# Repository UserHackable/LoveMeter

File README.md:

## LoveMeter 

### Board dimensions

* (390000, 110000) original units
* (3.9000, 1.1000) inches
* (99.0600, 27.9400) mm

[gerbers](%*_gerber.zip)

| Front | Back |
| --- | --- |
|  |  |

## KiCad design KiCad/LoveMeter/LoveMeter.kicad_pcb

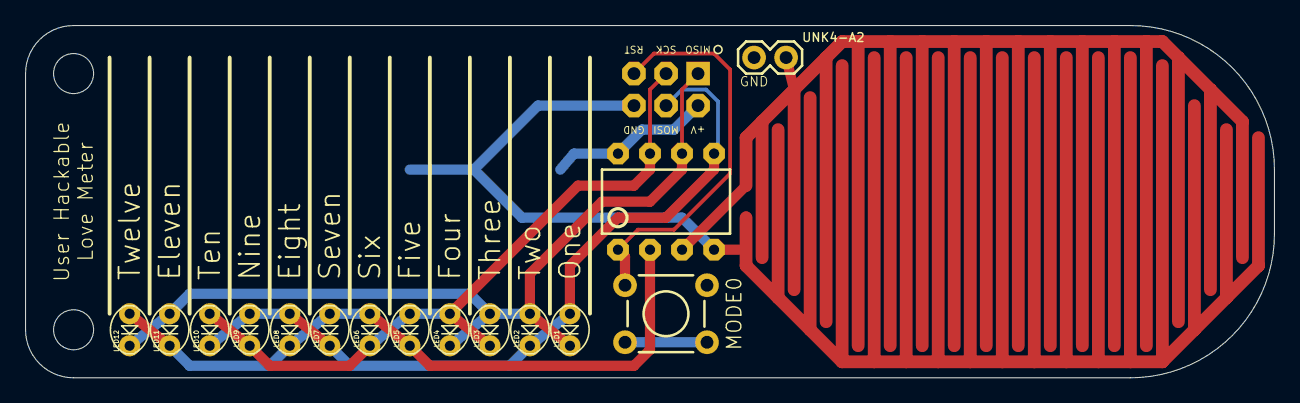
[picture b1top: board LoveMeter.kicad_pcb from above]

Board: 2 copper layers, 99.1 x 27.9 mm, 20 parts (1 on the bottom side), 8 nets.

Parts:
J1: AVR_SPI; 2X3-NS
LED1, LED2, LED3, LED4, LED5, LED6, LED7, LED8, LED9, LED10, LED11, LED12: LED-OVAL
MODE0: TACTILE-PTH
U1: TINY85; DIP08
U$3: THUMB_PAD
U$4: CR2032_STRAP
UNK4-A2: 1X02
UNK_HOLE_0: dummyfp0
UNK_HOLE_1: dummyfp1

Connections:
B0: J1.4, LED1.ANODE, LED2.CATHODE, LED7.CATHODE, LED8.ANODE, LED9.ANODE, LED10.CATHODE, U1.5
B1: J1.1, LED1.CATHODE, LED2.ANODE, LED3.ANODE, LED4.CATHODE, LED11.ANODE, LED12.CATHODE, U1.6
B2: J1.3, LED3.CATHODE, LED4.ANODE, LED5.ANODE, LED6.CATHODE, LED9.CATHODE, LED10.ANODE, U1.7
B3: LED5.CATHODE, LED6.ANODE, LED7.ANODE, LED8.CATHODE, LED11.CATHODE, LED12.ANODE, U1.2
B4: U1.3, U$3.2, UNK4-A2.2
GND: J1.6, MODE0.1, MODE0.2, U1.4, U$3.1, U$4.-, UNK4-A2.1
RST: J1.5, MODE0.4, U1.1
VCC: J1.2, U1.8, U$4.+2

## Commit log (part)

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2016-04-06 updating images
2016-04-07 from Makefile
